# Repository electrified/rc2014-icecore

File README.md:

## Board to interface BlackIce MX IceCore with RC2014 level converter.

For use with the level shifter board available here: https://github.com/electrified/level-shifter

## License

Copyright Ed Brindley 2020.

This source describes Open Hardware and is licensed under the CERN-OHL-P v2
You may redistribute and modify this documentation and make products using it under the terms of the CERN-OHL-P v2 (https:/cern.ch/cern-ohl). This documentation is distributed WITHOUT ANY EXPRESS OR IMPLIED WARRANTY, INCLUDING OF MERCHANTABILITY, SATISFACTORY QUALITY AND FITNESS FOR A PARTICULAR PURPOSE. Please see the CERN-OHL-P v2 for applicable conditions

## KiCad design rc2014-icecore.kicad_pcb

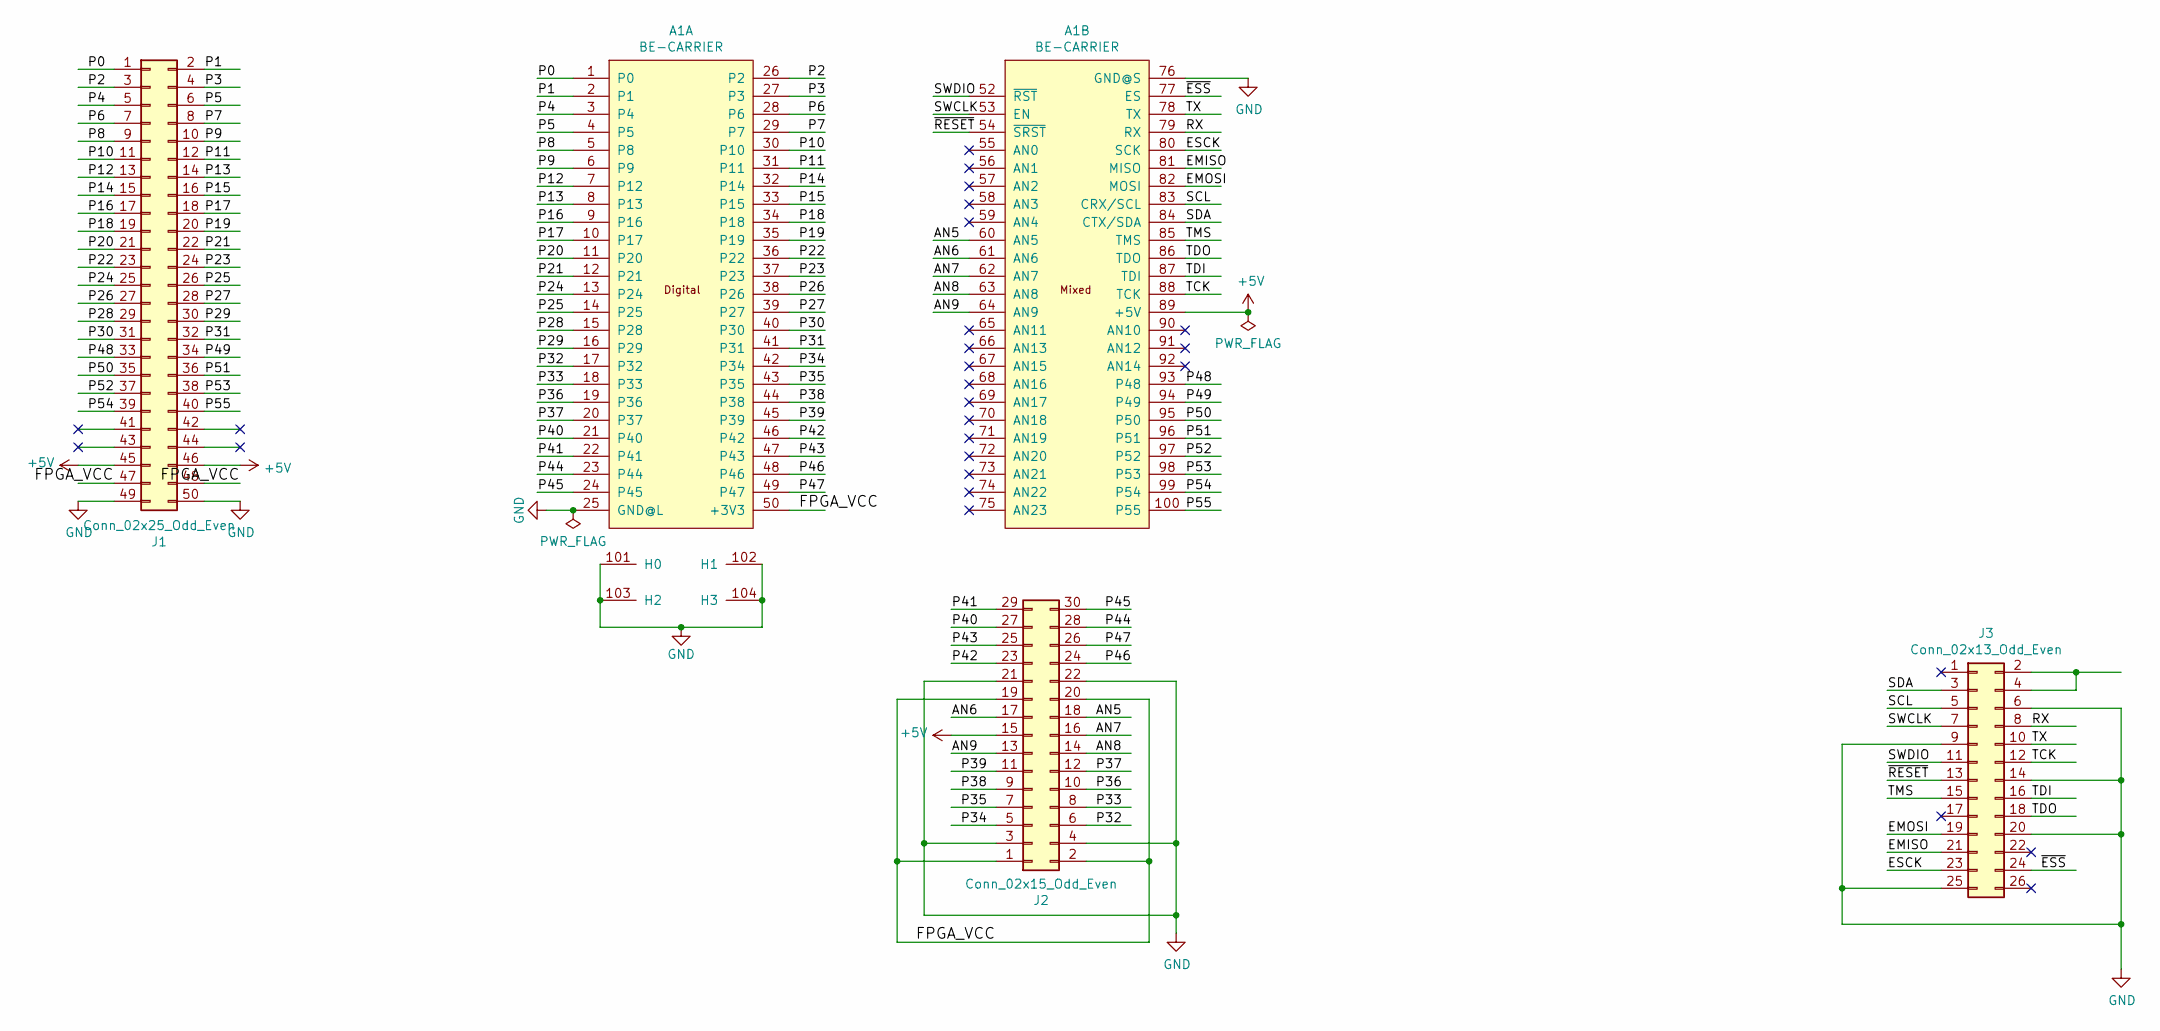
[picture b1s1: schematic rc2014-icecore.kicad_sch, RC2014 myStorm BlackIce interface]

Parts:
A1: BE-CARRIER; BE-CARRIER-SMD
J1: Conn_02x25_Odd_Even; PinHeader_2x25_P2.54mm_Vertical
J2: Conn_02x15_Odd_Even; PinSocket_2x15_P2.54mm_Vertical
J3: Conn_02x13_Odd_Even; PinHeader_2x13_P2.54mm_Vertical

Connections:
+5V: A1.89 (+5V), J1.45, J1.46, J2.15
/AN5: A1.60 (AN5), J2.18
/AN6: A1.61 (AN6), J2.17
/AN7: A1.62 (AN7), J2.16
/AN8: A1.63 (AN8), J2.14
/AN9: A1.64 (AN9), J2.13
/EMISO: A1.81 (MISO), J3.21
/EMOSI: A1.82 (MOSI), J3.19
/ESCK: A1.80 (SCK), J3.23
/FPGA_VCC: A1.50 (+3V3), J1.47, J1.48, J2.1, J2.2, J2.19, J2.20
/P0: A1.1 (P0), J1.1
/P1: A1.2 (P1), J1.2
/P2: A1.26 (P2), J1.3
/P3: A1.27 (P3), J1.4
/P4: A1.3 (P4), J1.5
/P5: A1.4 (P5), J1.6
/P6: A1.28 (P6), J1.7
/P7: A1.29 (P7), J1.8
/P8: A1.5 (P8), J1.9
/P9: A1.6 (P9), J1.10
/P10: A1.30 (P10), J1.11
/P11: A1.31 (P11), J1.12
/P12: A1.7 (P12), J1.13
/P13: A1.8 (P13), J1.14
/P14: A1.32 (P14), J1.15
/P15: A1.33 (P15), J1.16
/P16: A1.9 (P16), J1.17
/P17: A1.10 (P17), J1.18
/P18: A1.34 (P18), J1.19
/P19: A1.35 (P19), J1.20
/P20: A1.11 (P20), J1.21
/P21: A1.12 (P21), J1.22
/P22: A1.36 (P22), J1.23
/P23: A1.37 (P23), J1.24
/P24: A1.13 (P24), J1.25
/P25: A1.14 (P25), J1.26
/P26: A1.38 (P26), J1.27
/P27: A1.39 (P27), J1.28
/P28: A1.15 (P28), J1.29
/P29: A1.16 (P29), J1.30
/P30: A1.40 (P30), J1.31
/P31: A1.41 (P31), J1.32
/P32: A1.17 (P32), J2.6
/P33: A1.18 (P33), J2.8
/P34: A1.42 (P34), J2.5
/P35: A1.43 (P35), J2.7
/P36: A1.19 (P36), J2.10
/P37: A1.20 (P37), J2.12
/P38: A1.44 (P38), J2.9
/P39: A1.45 (P39), J2.11
/P40: A1.21 (P40), J2.27
/P41: A1.22 (P41), J2.29
/P42: A1.46 (P42), J2.23
/P43: A1.47 (P43), J2.25
/P44: A1.23 (P44), J2.28
/P45: A1.24 (P45), J2.30
/P46: A1.48 (P46), J2.24
/P47: A1.49 (P47), J2.26
/P48: A1.93 (P48), J1.33
/P49: A1.94 (P49), J1.34
/P50: A1.95 (P50), J1.35
/P51: A1.96 (P51), J1.36
/P52: A1.97 (P52), J1.37
/P53: A1.98 (P53), J1.38
/P54: A1.99 (P54), J1.39
/P55: A1.100 (P55), J1.40
/RX: A1.79 (RX), J3.8
/SCL: A1.83 (CRX/SCL), J3.5
/SDA: A1.84 (CTX/SDA), J3.3
/SWCLK: A1.53 (EN), J3.7
/SWDIO: A1.52 (~RST), J3.11
/TCK: A1.88 (TCK), J3.12
/TDI: A1.87 (TDI), J3.16
/TDO: A1.86 (TDO), J3.18
/TMS: A1.85 (TMS), J3.15
/TX: A1.78 (TX), J3.10
/~ESS: A1.77 (ES), J3.24
/~RESET: A1.54 (~SRST), J3.13
GND: A1.25 (GND@L), A1.76 (GND@S), A1.101 (H0), A1.102 (H1), A1.103 (H2), A1.104 (H3), J1.49, J1.50, J2.3, J2.4, J2.21, J2.22, J3.6, J3.9, J3.14, J3.20, J3.25
unnamed: J3.2, J3.4

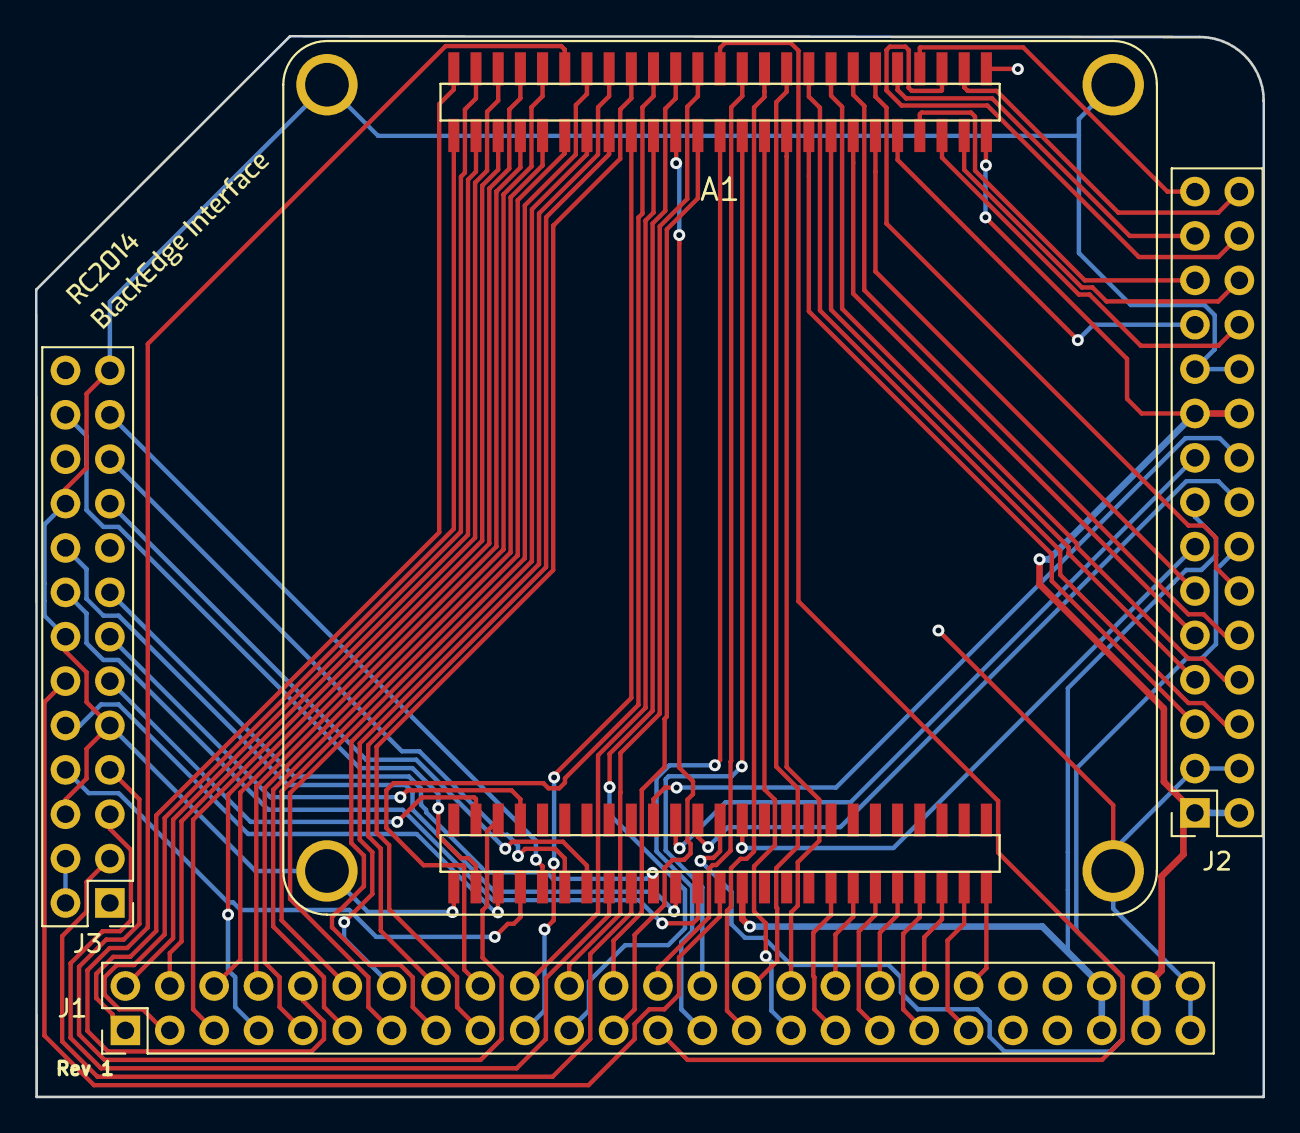
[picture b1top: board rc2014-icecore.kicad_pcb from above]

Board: 2 copper layers, 70.3 x 60.7 mm, 4 parts (0 on the bottom side), 80 nets.

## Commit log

2020-10-04 INitial version with half implemented VGA
2020-10-11 Board routed
2020-10-12 Board redesign
2020-10-16 2nd redesign
2020-10-16 remove redundant files
2020-10-18 reorder pmod pins
2020-10-22 Rev 1 as sent to JLCPCB
2021-06-11 Check in old changes
2021-06-11 Start new merged design
2021-06-25 Add build action
2021-06-28 Further work on combining boards - still WIP
2021-06-29 partially routed
2023-01-29 Update to Kicad 6
2023-01-29 Further Kicad 6 updates
2023-09-17 Update to kicad 7
